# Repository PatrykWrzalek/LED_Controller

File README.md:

# LED_Controller Project

## Project Summary

**LED_Controller** is a versatile ESP32-C6 based project designed for advanced LED strip control. The system integrates multiple LED types, including light **COLD**, **WARM** (PWM controlled), and **WS2812 addressable RGB LEDs**, and can be controlled via both **IR remote (NEC protocol)** and **smartphone over WiFi**.  

Key project features:
- Multi-tasking architecture using **FreeRTOS**.
- LED control abstraction for PWM and WS2812 LEDs.
- IR remote control (NEC standard) with event-driven handling.
- WiFi connectivity with **HTTP API** for remote LED control.
- Persistent settings storage using **NVS**, allowing saved color and brightness presets.
- Over-the-Air (**OTA**) updates for firmware maintenance.
- Debugging infrastructure including **Console** and **GDB Stub**.
- **Watchdog** integration to prevent system hangs.
- Optional MQTT / RainMaker integration for cloud-based control.

The project is structured with **modular components**, making it easy to extend or adapt for additional hardware or features.  

---

## Project Development Roadmap

Track progress with the checkboxes below:

- [x] Hello World / ESP32-C6 Setup  
- [x] Console setup for early debugging  
- [ ] Watchdog integration  
- [ ] FreeRTOS task architecture & event queues  
- [ ] PWM LED control (light COLD & WARM)  
- [ ] WS2812 LED control (RMT)  
- [ ] IR NEC remote control  
- [ ] NVS settings storage  
- [ ] WiFi station connection  
- [ ] HTTP Server / API endpoints  
- [ ] Web-based control UI  
- [ ] OTA firmware updates  
- [ ] MQTT / RainMaker integration (optional)

---

## Recommended Architecture

- **led_task** — handles all LED output (PWM + WS2812)  
- **ir_task** — decodes IR commands and sends events to led_task  
- **wifi_task** — manages WiFi connectivity  
- **web_server_task** — provides HTTP API and web UI  
- **settings_task** — handles NVS read/write  
- **ota_task** — manages OTA updates  
- **watchdog_task** — monitors system health  
- **console_task** — allows command-line interaction and debugging  

Communication between tasks is fully **event-driven** via FreeRTOS queues, ensuring safe and efficient task execution.

---

## Hardware

- ESP32-C6 (Seeed Studio development board recommended)  
- LED Types:
  - COLD LED (PWM)
  - WARM LED (PWM)
  - WS2812 addressable RGB LED strip
- IR receiver (NEC protocol)

---

## Development Notes

- Focus on building **Console + Watchdog** early for stable debugging.  
- Use **LEDC example** for PWM LEDs and **RMT/LED Strip example** for WS2812.  
- Leverage **NVS** to store user preferences like default color and brightness.  
- Start with **HTTP + Web UI**, later consider **MQTT/RainMaker** for cloud integration.  
- OTA updates should only be tested once system is stable.

---

This README provides a clear project overview and a step-by-step development plan for anyone who wants to contribute or replicate the project.

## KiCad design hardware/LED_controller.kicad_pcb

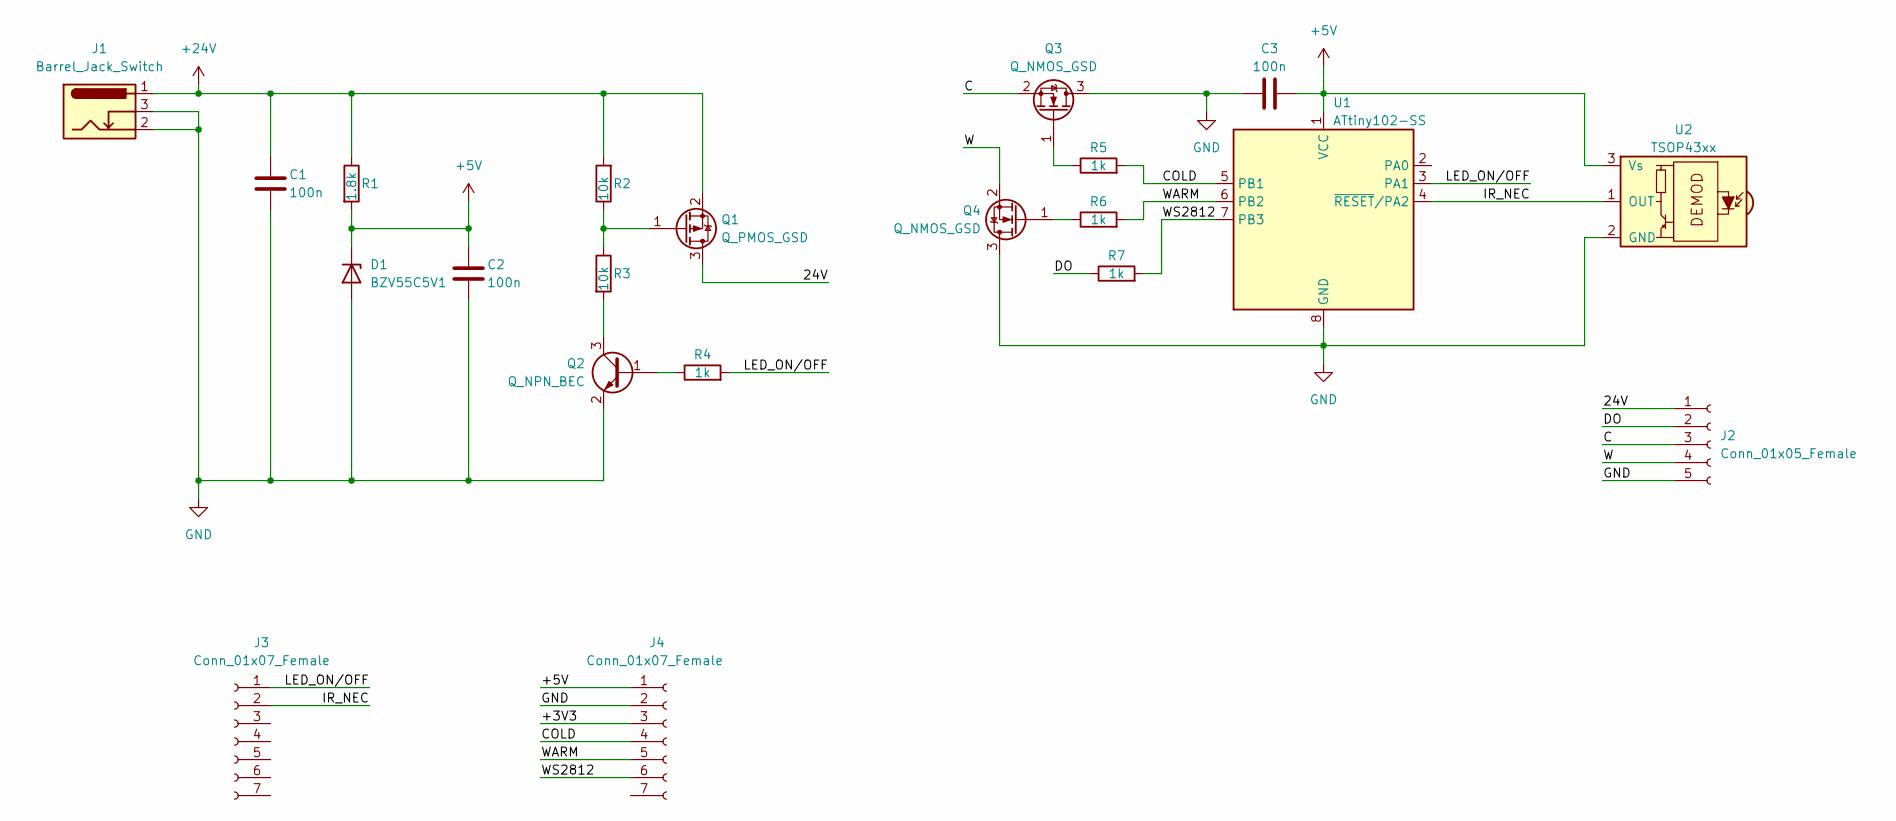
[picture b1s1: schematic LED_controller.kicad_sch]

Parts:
C1, C2, C3: 100n; C_0603_1608Metric_Pad1.08x0.95mm_HandSolder
D1: BZV55C5V1; D_1206_3216Metric_Pad1.42x1.75mm_HandSolder
J1: Barrel_Jack_Switch; BarrelJack_GCT_DCJ200-10-A_Horizontal
J2: Conn_01x05_Female; PinHeader_1x05_P2.54mm_Vertical
J3, J4: Conn_01x07_Female; PinSocket_1x07_P2.54mm_Vertical
Q1: Q_PMOS_GSD; TSOT-23
Q2: Q_NPN_BEC; TSOT-23
Q3, Q4: Q_NMOS_GSD; TSOT-23
R1: 1.8k; R_1206_3216Metric_Pad1.30x1.75mm_HandSolder
R2, R3: 10k; R_0603_1608Metric_Pad0.98x0.95mm_HandSolder
R4, R5, R6, R7: 1k; R_0805_2012Metric_Pad1.20x1.40mm_HandSolder
U1: ATtiny102-SS; SOIC-8_3.9x4.9mm_P1.27mm
U2: TSOP43xx; Vishay_MOLD-3Pin

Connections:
+5V: C2.1, C3.2, D1.1 (K), J4.1, R1.2, U1.1 (VCC), U2.3 (Vs)
+24V: C1.1, J1.1, Q1.2 (S), R1.1, R2.2
/24V: J2.1, Q1.3 (D)
/+3V3: J4.3
/C: J2.3, Q3.2 (S)
/COLD: J4.4, R5.2, U1.5 (PB1)
/DO: J2.2, R7.1
/IR_NEC: J3.2, U1.4 (~RESET/PA2), U2.1 (OUT)
/LED_ON/OFF: J3.1, R4.2, U1.3 (PA1)
/W: J2.4, Q4.2 (S)
/WARM: J4.5, R6.2, U1.6 (PB2)
/WS2812: J4.6, R7.2, U1.7 (PB3)
GND: C1.2, C2.2, C3.1, D1.2 (A), J1.2, J1.3, J2.5, J4.2, Q2.2 (E), Q3.3 (D), Q4.3 (D), U1.8 (GND), U2.2 (GND)
unnamed: Q1.1 (G), R2.1, R3.1
unnamed: Q2.1 (B), R4.1
unnamed: Q2.3 (C), R3.2
unnamed: Q3.1 (G), R5.1
unnamed: Q4.1 (G), R6.1

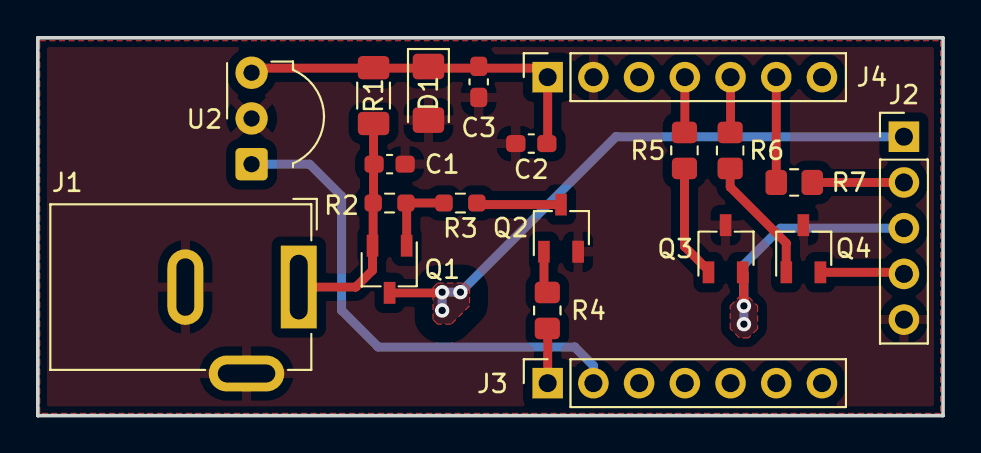
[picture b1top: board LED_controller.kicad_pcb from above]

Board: 2 copper layers, 50.3 x 21.0 mm, 20 parts (0 on the bottom side), 17 nets.

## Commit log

2026-02-18 Create New Blank Project
2026-02-18 Test example for status_led
2026-02-18 Enhance README with project details and roadmap
    Added project summary, development roadmap, recommended architecture, hardware requirements, and development notes to README.
2026-02-18 Test Hello_world!
2026-02-18 Update LED types from White/Yellow to COLD/WARM
2026-02-18 Clarify LED types in project summary
    Updated project summary to clarify LED types.
2026-02-19 Add LED_controller KiCad project and Gerbers
    Add complete KiCad project and manufacturing outputs for the LED_controller PCB.
2026-02-22 Add LED driver and event bus components
2026-02-22 Add debug_console and make drv_led configurable
2026-02-22 Add debug console component with REPL
2026-02-22 Add event_bus_emit and wire up event flow
2026-02-23 Add LED CLI and refactor event bus/LED driver
2026-02-24 Add app_config and improve task/event APIs
2026-02-25 Migrate app_config.h to Kconfig options
2026-02-25 Convert drv_led API to esp_err_t and add guards
2026-02-26 Extract LED CLI into drv_led_cli component
2026-02-26 Update checkbox status for console setup
2026-03-08 Restructure components and add system_monitor
2026-03-09 Introduce app_start and shared app events
2026-03-09 Add system monitor and integrate modules
2026-03-10 Integrate and implement system monitor
2026-03-11 Revert "Merge system_monitor CLI into core module for test"
    This reverts commit 8bbe357541d04f6ce3e2f13692a1dfa69c773fbb.
2026-03-11 Move debug_console dep to system_monitor
2026-03-12 Refactor system monitor to dynamic task registry
